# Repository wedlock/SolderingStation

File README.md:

# SolderingStation
Arduino PID soldering station

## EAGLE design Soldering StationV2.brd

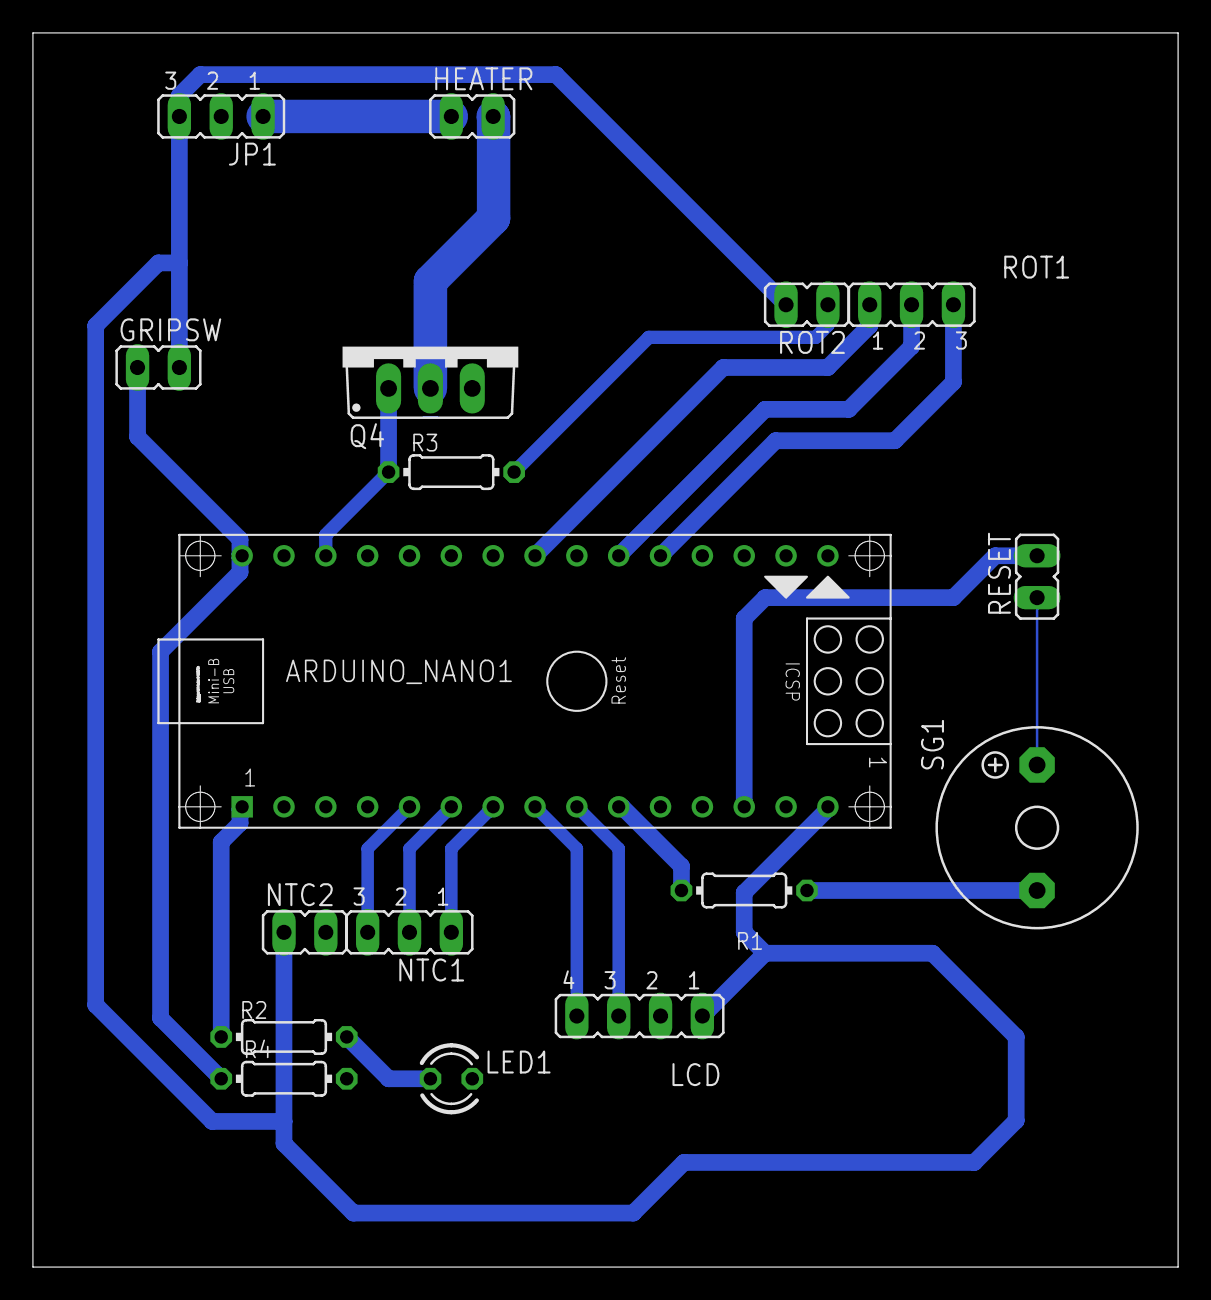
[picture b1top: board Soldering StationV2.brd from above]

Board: 2 copper layers, 69.5 x 74.9 mm, 17 parts (0 on the bottom side), 19 nets.

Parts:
ARDUINO_NANO1: ARDUINO_NANO
GRIPSW: JP1
HEATER: 794681-2; JP1
JP1: JP2
LCD: JP4
LED1: LED3MM
NTC1: JP2
NTC2: JP1
Q4: IRLB8721; TO220BV
R1, R2: 1K; 0204/7
R3, R4: 4.7k; 0204/7
RESET: JP1
ROT1: JP2
ROT2: JP1
SG1: F/TMB

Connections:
+5V: ARDUINO_NANO1.15, GRIPSW.2, JP1.3, LCD.1, NTC2.1, ROT2.2
+24V: HEATER.1, JP1.1
BUZZER: ARDUINO_NANO1.10, R1.2
GND: ARDUINO_NANO1.14, ARDUINO_NANO1.19, JP1.2, LCD.2, LED1.K, NTC2.2, Q4.S, R3.2, R4.2, RESET.1, ROT2.1, SG1.+
LED: ARDUINO_NANO1.1, R2.2
unnamed: ARDUINO_NANO1.28, Q4.G, R3.1
unnamed: ARDUINO_NANO1.21, ROT1.2
unnamed: R1.1, SG1.-
unnamed: LED1.A, R2.1
unnamed: ARDUINO_NANO1.30, GRIPSW.1, R4.1
unnamed: ARDUINO_NANO1.20, ROT1.3
unnamed: ARDUINO_NANO1.5, NTC1.3
unnamed: ARDUINO_NANO1.6, NTC1.2
unnamed: HEATER.2, Q4.D
unnamed: ARDUINO_NANO1.9, LCD.3
unnamed: ARDUINO_NANO1.8, LCD.4
unnamed: ARDUINO_NANO1.7, NTC1.1
unnamed: ARDUINO_NANO1.23, ROT1.1
RESET: ARDUINO_NANO1.13, RESET.2
